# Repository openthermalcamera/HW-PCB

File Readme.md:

# Open Thermal Camera - KiCad PCB
This repository contains KiCad source files for Open Thermal Camera PCB.

The PCB is 2 layer, thickness of 0.8mm (To accommodate the edge TypeC / MicroUSB connector)

Under releases you can find:
- Interactive BOM (.html)
- KiCost BOM (.xlsx)
- Gerbers
- Position files (.pos & .rpt)

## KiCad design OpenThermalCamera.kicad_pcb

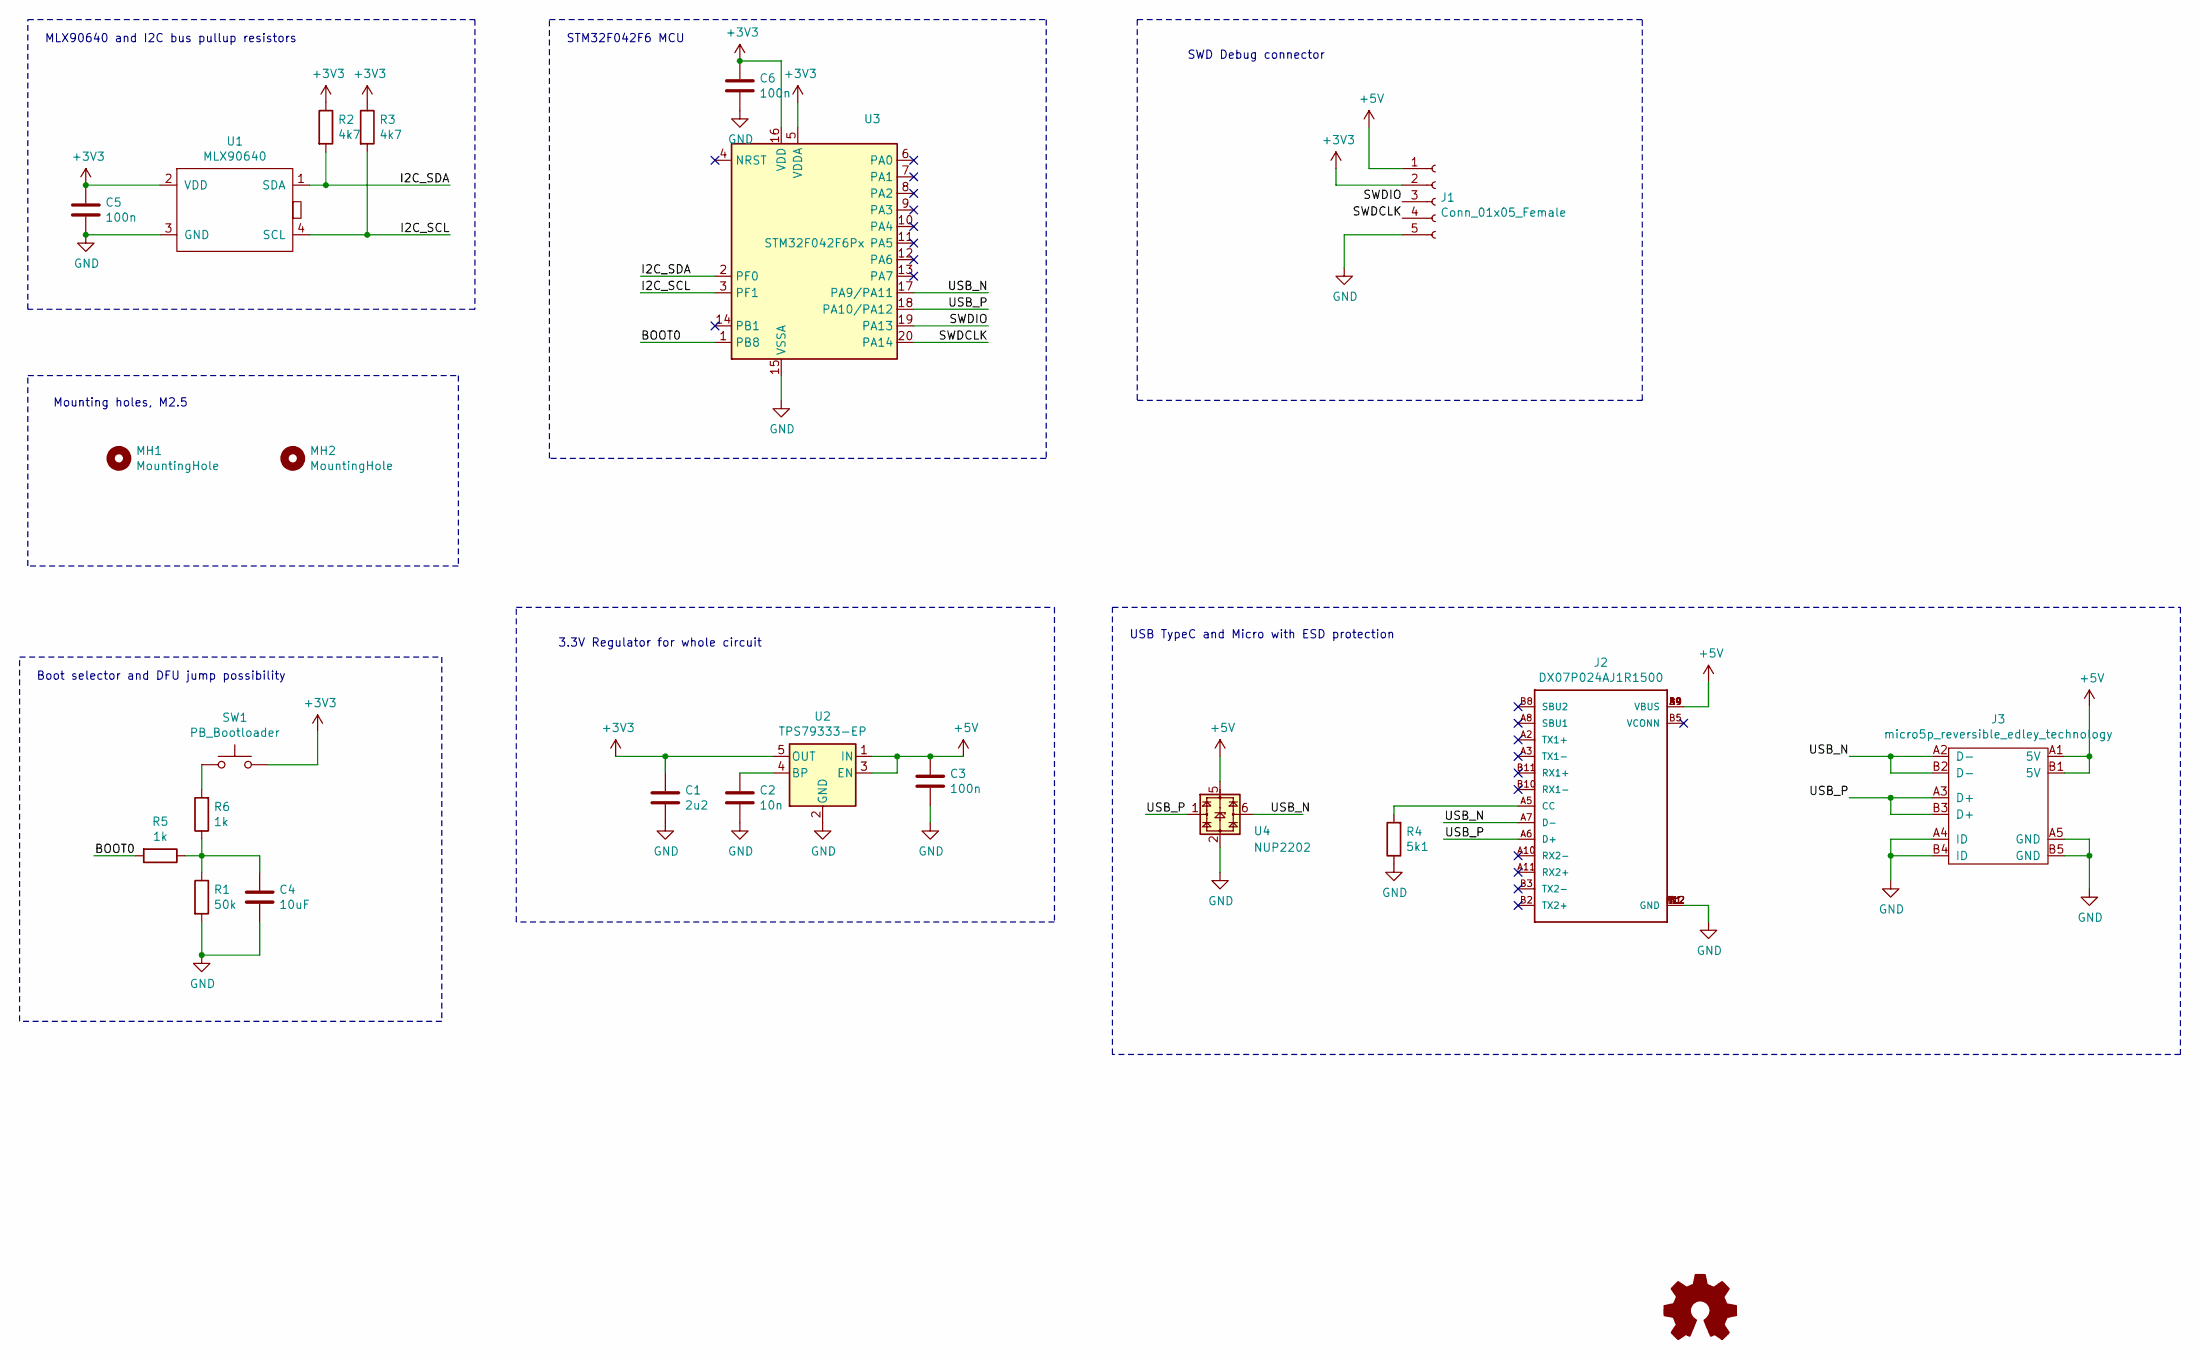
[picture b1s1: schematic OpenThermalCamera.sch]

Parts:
C1: 2u2; C_0805_2012Metric_Pad1.15x1.40mm_HandSolder; Part Number 2896530
C2: 10n; C_0805_2012Metric_Pad1.15x1.40mm_HandSolder; Part Number 2534050
C3, C6: 100n; C_0805_2012Metric_Pad1.15x1.40mm_HandSolder; Part Number 2496943
C4: 10uF; C_0805_2012Metric_Pad1.15x1.40mm_HandSolder; mfr# C2012X5R1C106K085AC
C5: 100n; C_0805_2012Metric_Pad1.15x1.40mm_HandSolder; mfr# 0805B104K250CT
G1: Logo_Open_Hardware_Small; OSHW-Logo2_7.3x6mm_SilkScreen
J1: Conn_01x05_Female; PinHeader_1x05_P1.27mm_Vertical
J2: DX07P024AJ1R1500; Part Number 656-DX07P024AJ1R1500
J3: micro5p_reversible_edley_technology; reversible_micro_usb
MH1, MH2: MountingHole; MountingHole_2.7mm_M2.5
R1: 50k; R_0805_2012Metric_Pad1.15x1.40mm_HandSolder; mfr# CRCW080551K0JNEA
R2, R3: 4k7; R_0805_2012Metric_Pad1.15x1.40mm_HandSolder; mfr# CRCW08054K70FKEA
R4: 5k1; R_0805_2012Metric_Pad1.15x1.40mm_HandSolder; mfr# CRCW08055K10FKEAC
R5, R6: 1k; R_0805_2012Metric_Pad1.15x1.40mm_HandSolder; mfr# CRCW08051K00FKEAC
SW1: PB_Bootloader; SolderJumper-2_P1.3mm_Open_RoundedPad1.0x1.5mm; Part Number /
U1: MLX90640; Part Number 482-MLX90640ESFBABSP
U2: TPS79333-EP; SOT-23-5; mfr# TPS79333DBVR
U3: STM32F042F6Px; TSSOP-20_4.4x6.5mm_P0.65mm; Part Number 511-STM32F042F6P6TR
U4: NUP2202; SOT-363_SC-70-6; Part Number 2533276

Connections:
+3V3: C1.1, C5.1, C6.1, J1.2, R2.1, R3.1, SW1.2, U1.2 (VDD), U2.5 (OUT), U3.5 (VDDA), U3.16 (VDD)
+5V: C3.1, J1.1, J2.A4 (VBUS), J2.A9 (VBUS), J2.B4 (VBUS), J2.B9 (VBUS), J3.A1 (5V), J3.B1 (5V), U2.1 (IN), U2.3 (EN), U4.5
/BOOT0: R5.2, U3.1 (PB8)
/I2C_SCL: R3.2, U1.4 (SCL), U3.3 (PF1)
/I2C_SDA: R2.2, U1.1 (SDA), U3.2 (PF0)
/SWDCLK: J1.4, U3.20 (PA14)
/SWDIO: J1.3, U3.19 (PA13)
/USB_N: J2.A7 (D-), J3.A2 (D-), J3.B2 (D-), U3.17 (PA9/PA11), U4.6
/USB_P: J2.A6 (D+), J3.A3 (D+), J3.B3 (D+), U3.18 (PA10/PA12), U4.1
GND: C1.2, C2.2, C3.2, C4.2, C5.2, C6.2, J1.5, J2.A1 (GND), J2.A12 (GND), J2.B1 (GND), J2.B12 (GND), J3.A4 (ID), J3.A5 (GND), J3.B4 (ID), J3.B5 (GND), R1.2, R4.1, U1.3 (GND), U2.2 (GND), U3.15 (VSSA), U4.2
unnamed: C2.1, U2.4 (BP)
unnamed: C4.1, R1.1, R5.1, R6.1
unnamed: J2.A5 (CC), R4.2
unnamed: R6.2, SW1.1

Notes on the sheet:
SWD Debug connector
USB TypeC and Micro with ESD protection
3.3V Regulator for whole circuit
MLX90640 and I2C bus pullup resistors
STM32F042F6 MCU
Boot selector and DFU jump possibility
Mounting holes, M2.5

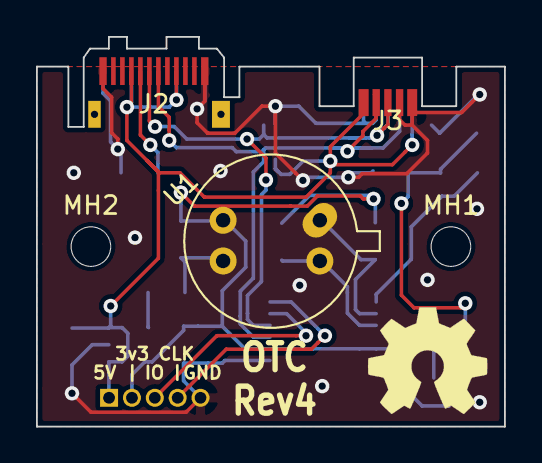
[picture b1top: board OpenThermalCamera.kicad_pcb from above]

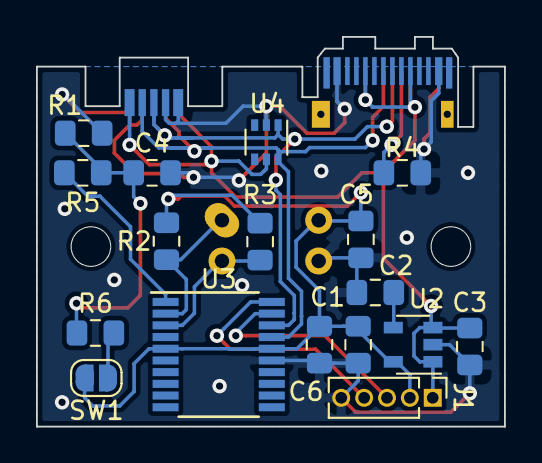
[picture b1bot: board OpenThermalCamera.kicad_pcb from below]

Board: 2 copper layers, 26.0 x 21.6 mm, 23 parts (17 on the bottom side), 14 nets.

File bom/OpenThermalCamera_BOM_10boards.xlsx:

Item | Qty | Reference(s) | Value | Footprint | Part Number | Supplier
1 | 10 | C1 | 2u2 | Capacitor_SMD:C_0805_2012Metric_Pad1.15x1.40mm_HandSolder | 2896530 | Farnell
2 | 10 | C2 | 10n | Capacitor_SMD:C_0805_2012Metric_Pad1.15x1.40mm_HandSolder | 2534050 | Farnell
3 | 30 | C3, C5, C6 | 100n | Capacitor_SMD:C_0805_2012Metric_Pad1.15x1.40mm_HandSolder | 2496943 | Farnell
4 | 10 | C4 | 1uF | Capacitor_SMD:C_0805_2012Metric_Pad1.15x1.40mm_HandSolder | 2534058 | Farnell
5 | 10 | J1 | Conn_ARM_JTAG_SWD_10 | Connector_PinHeader_1.27mm:PinHeader_2x05_P1.27mm_Vertical_SMD | 2886068 | Farnell
8 | 10 | R1 | 10k | Resistor_SMD:R_0805_2012Metric_Pad1.15x1.40mm_HandSolder | 2502786 | Farnell
9 | 20 | R2, R3 | 4k7 | Resistor_SMD:R_0805_2012Metric_Pad1.15x1.40mm_HandSolder | 1653013 | Farnell
10 | 10 | SW1 | PB_Bootloader | Button_Switch_SMD:SW_SPST_FSMSM | 2468741 | Farnell
12 | 10 | U2 | TPS793333-EP | Package_TO_SOT_SMD:SOT-23-5_HandSoldering | 1470478 | Farnell
13 | 10 | U3 | STM32F042F6Px | Package_SO:TSSOP-20_4.4x6.5mm_P0.65mm | 2469549 | Farnell
14 | 10 | U4 | NUP2202 | Package_TO_SOT_SMD:SOT-363_SC-70-6 | 2533276 | Farnell

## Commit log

2018-12-03 Rev2
2018-12-11 Rev3: fixed MLX90640 footprint
2018-12-12 Fixed USB Type-C edge cuts
2019-02-19 Added solder mask on MLX sensor pads
2019-03-01 Preperations for Rev3
2019-03-01 First Rev3-M commit
2019-03-01 First Rev3-C commit
2019-07-26 Added a license
2019-09-21 Fixed reversible microusb footprint
2019-09-21 Added readme file
2019-09-21 Readme relative path fix
2019-09-21 Readme image fix
2019-09-30 Added additional PCB information
